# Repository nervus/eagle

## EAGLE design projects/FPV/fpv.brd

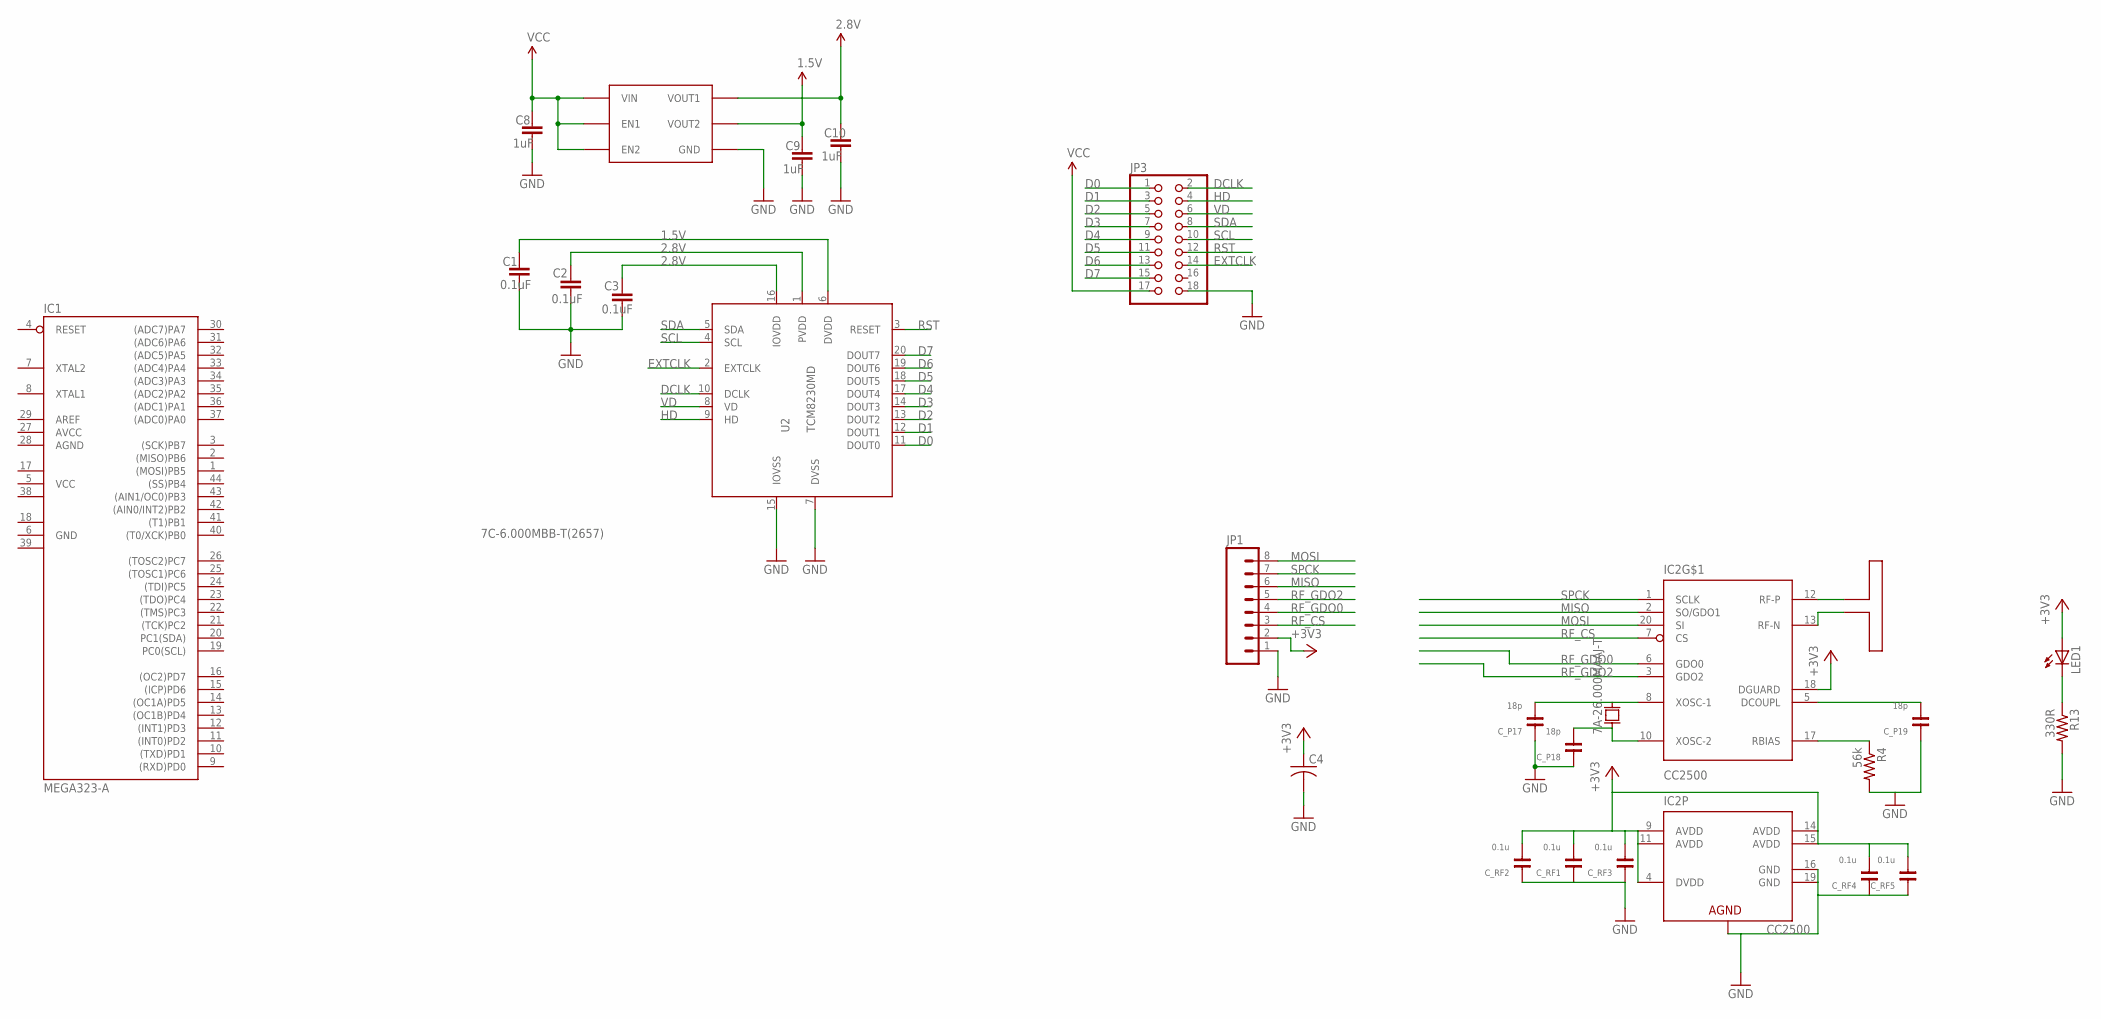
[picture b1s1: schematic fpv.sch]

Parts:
C1, C2, C3: 0.1uF; 0402-CAP
C4: C-USC1206; C1206
C8, C9, C10: 1uF; 0402-CAP
C_P17, C_P18, C_P19: 18p; 0603-CAP
C_RF1, C_RF2, C_RF3, C_RF4, C_RF5: 0.1u; 0603-CAP
IC1: MEGA323-A; TQFP44
IC2: CC2500; QLP-20
JP1: M081X08; 1X08
JP3: PINHD-2X9; 2X09
LED1: LED1206; LED-1206
R4: 56k; 0402-RES
R13: 330R; 0402-RES
U1: MIC5320; SOT23-6
U2: TCM8230MD
U$22: ANTENNA_DIPOLE; CC2500_FOLDED_DIPOLE_ANTENNA
U$23: 7A-26.000MAAJ-T; 5X3.2MM_SMD_XTAL

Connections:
1.5V: C1.1, C9.1, U1.5 (VOUT2), U2.6 (DVDD)
2.8V: C2.1, C3.1, C10.1, U1.4 (VOUT1), U2.1 (PVDD), U2.16 (IOVDD)
+3V3: C4.1, C_RF1.2, C_RF2.2, C_RF3.2, C_RF4.2, C_RF5.2, IC2.4 (DVDD), IC2.9 (AVDD), IC2.11 (AVDD), IC2.14 (AVDD), IC2.15 (AVDD), IC2.18 (DGUARD), JP1.2, LED1.A
AGND: IC1.28 (AGND)
AVCC: IC1.27 (AVCC)
D0: JP3.1, U2.11 (DOUT0)
D1: JP3.3, U2.12 (DOUT1)
D2: JP3.5, U2.13 (DOUT2)
D3: JP3.7, U2.14 (DOUT3)
D4: JP3.9, U2.17 (DOUT4)
D5: JP3.11, U2.18 (DOUT5)
D6: JP3.13, U2.19 (DOUT6)
D7: JP3.15, U2.20 (DOUT7)
DCLK: JP3.2, U2.10 (DCLK)
DCOUPL: C_P19.2, IC2.5 (DCOUPL)
EXTCLK: JP3.14, U2.2 (EXTCLK)
GND: C1.2, C2.2, C3.2, C4.2, C8.2, C9.2, C10.2, C_P17.1, C_P18.1, C_P19.1, C_RF1.1, C_RF2.1, C_RF3.1, C_RF4.1, C_RF5.1, IC1.6 (GND), IC2.16 (GND), IC2.19 (GND), IC2.PAD (AGND), IC2.THERMAL1 (AGND), IC2.THERMAL2 (AGND), IC2.THERMAL3 (AGND), IC2.THERMAL4 (AGND), IC2.THERMAL5 (AGND), JP1.1, JP3.18, R4.2, R13.2, U1.2 (GND), U2.7 (DVSS), U2.15 (IOVSS)
GND1: IC1.18 (GND1)
GND2: IC1.39 (GND2)
HD: JP3.4, U2.9 (HD)
MISO: IC2.2 (SO/GDO1), JP1.6
MOSI: IC2.20 (SI), JP1.8
unnamed: LED1.C, R13.1
unnamed: IC2.12 (RF-P), U$22.P$1
unnamed: IC2.13 (RF-N), U$22.P$2
unnamed: C_P17.2, IC2.8 (XOSC-1), U$23.X2
unnamed: C_P18.2, IC2.10 (XOSC-2), U$23.X1
unnamed: IC2.17 (RBIAS), R4.1
RF_CS: IC2.7 (CS), JP1.3
RF_GDO0: IC2.6 (GDO0), JP1.4
RF_GDO2: IC2.3 (GDO2), JP1.5
RST: JP3.12, U2.3 (RESET)
SCL: JP3.10, U2.4 (SCL)
SDA: JP3.8, U2.5 (SDA)
SPCK: IC2.1 (SCLK), JP1.7
VCC: C8.1, IC1.5 (VCC), JP3.17, U1.1 (EN2), U1.3 (VIN), U1.6 (EN1)
VCC1: IC1.17 (VCC1)
VCC2: IC1.38 (VCC2)
VD: JP3.6, U2.8 (VD)

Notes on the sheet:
7C-6.000MBB-T(2657)

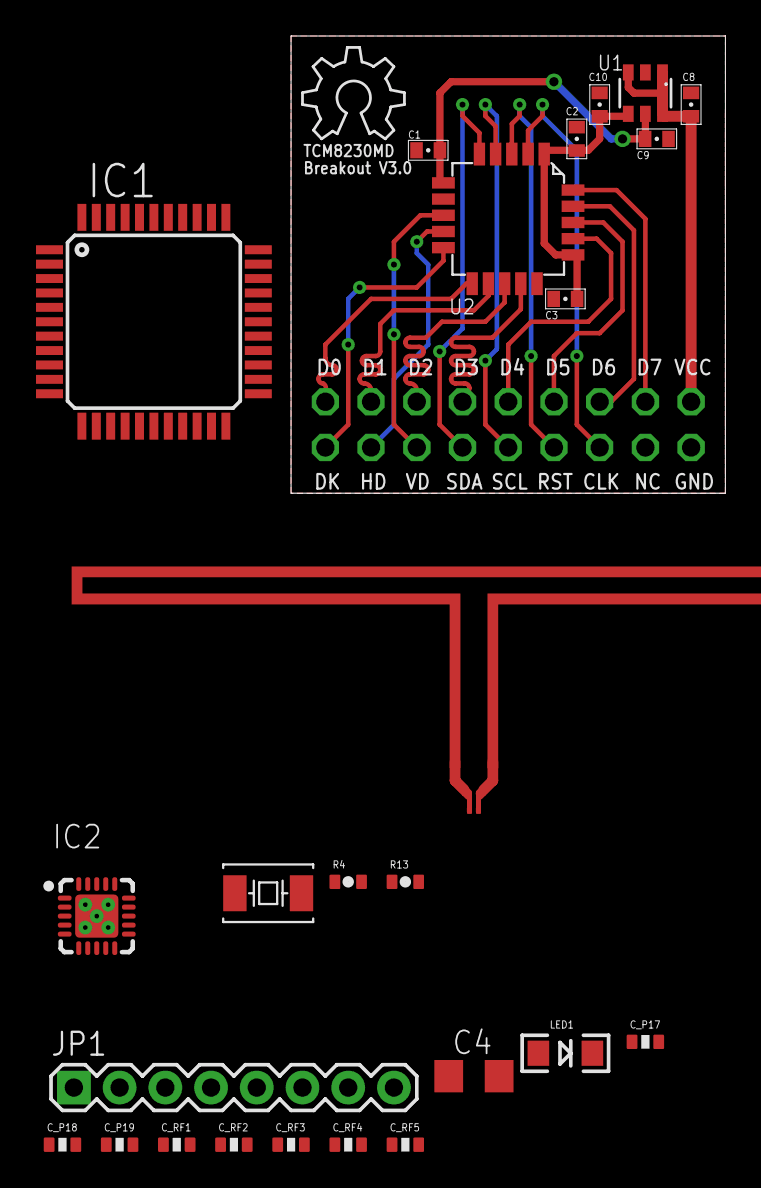
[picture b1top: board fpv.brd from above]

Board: 2 copper layers, 24.1 x 25.4 mm, 27 parts (1 on the bottom side), 33 nets.

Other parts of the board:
U$5: OSHW_6X200_NOTEXT

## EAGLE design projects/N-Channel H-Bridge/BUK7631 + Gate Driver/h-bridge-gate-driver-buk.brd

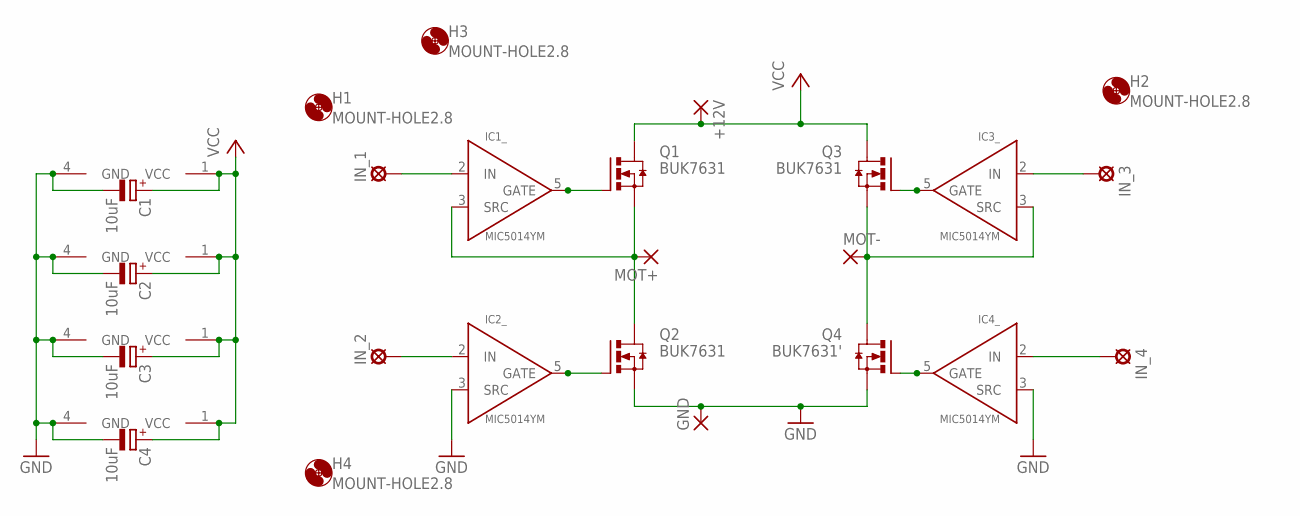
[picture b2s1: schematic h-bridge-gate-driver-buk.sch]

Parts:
+12V: WIREPAD4,16O1,6; 4,16O1,6
C1, C2, C3, C4: 10uF; UD-4X5,8_NICHICON
GND: WIREPAD4,16O1,6; 4,16O1,6
H1, H2, H3, H4: MOUNT-HOLE2.8; 2,8
IC1, IC2, IC3, IC4: MIC5014YM; SO8
IN_1, IN_2, IN_3, IN_4: LSP11
MOT+: WIREPAD4,16O1,6; 4,16O1,6
MOT-: WIREPAD4,16O1,6; 4,16O1,6
Q1, Q2, Q3: BUK7631; D2PAK_TO263
Q4: BUK7631'; D2PAK_TO263

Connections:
GND: C1.-, C2.-, C3.-, C4.-, GND.1, IC1.4 (GND), IC2.3 (SRC), IC2.4 (GND), IC3.4 (GND), IC4.3 (SRC), IC4.4 (GND), Q2.3 (S), Q4.3 (S)
MOT+: IC1.3 (SRC), MOT+.1, Q1.3 (S), Q2.4 (D)
MOT-: IC3.3 (SRC), MOT-.1, Q3.3 (S), Q4.4 (D)
unnamed: IC4.2 (IN), IN_4.MP
unnamed: IC3.5 (GATE), Q3.1 (G)
unnamed: IC1.2 (IN), IN_1.MP
unnamed: IC3.2 (IN), IN_3.MP
unnamed: IC2.2 (IN), IN_2.MP
unnamed: IC1.5 (GATE), Q1.1 (G)
unnamed: IC4.5 (GATE), Q4.1 (G)
unnamed: IC2.5 (GATE), Q2.1 (G)
VCC: +12V.1, C1.+, C2.+, C3.+, C4.+, IC1.1 (VCC), IC2.1 (VCC), IC3.1 (VCC), IC4.1 (VCC), Q1.4 (D), Q3.4 (D)

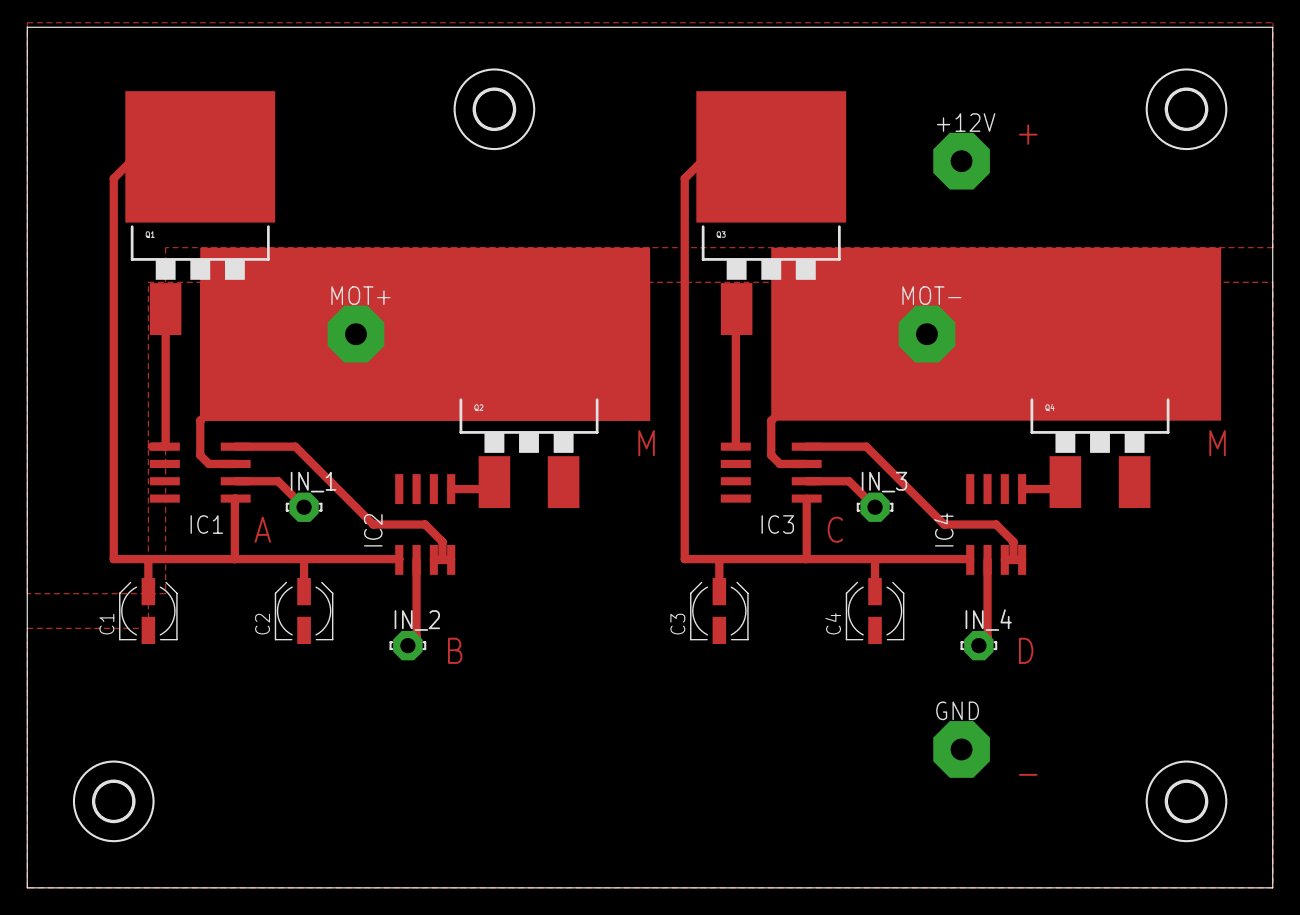
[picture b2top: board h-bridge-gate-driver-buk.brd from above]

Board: 2 copper layers, 91.4 x 63.2 mm, 24 parts (0 on the bottom side), 12 nets.

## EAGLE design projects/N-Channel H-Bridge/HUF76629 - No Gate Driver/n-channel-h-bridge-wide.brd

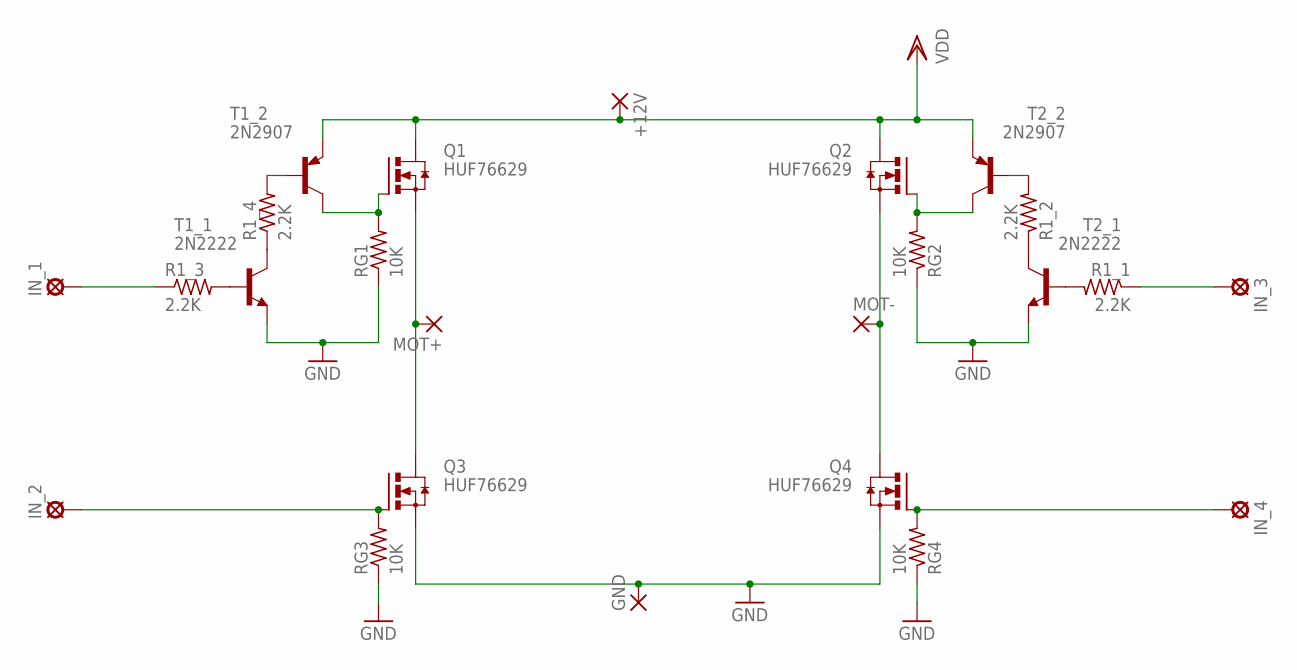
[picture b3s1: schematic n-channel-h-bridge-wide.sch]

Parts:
+12V: WIREPAD4,16O1,6; 4,16O1,6
GND: WIREPAD4,16O1,6; 4,16O1,6
IN_1, IN_2, IN_3, IN_4: LSP11
MOT+: WIREPAD4,16O1,6; 4,16O1,6
MOT-: WIREPAD4,16O1,6; 4,16O1,6
Q1, Q2, Q3, Q4: HUF76629; D-PAK_TO252
R1_1, R1_2, R1_3, R1_4: 2.2K; R0805
RG1, RG2, RG3, RG4: 10K; R0805
T1_1, T2_1: 2N2222; TO92-EBC-OVAL
T1_2, T2_2: 2N2907; TO92-EBC-OVAL

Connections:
B: IN_2.MP, Q3.1 (G), RG3.2
D: IN_4.MP, Q4.1 (G), RG4.2
GND: GND.1, Q3.3 (S), Q4.3 (S), RG1.1, RG2.1, RG3.1, RG4.1, T1_1.E, T2_1.E
unnamed: R1_1.2, T2_1.B
unnamed: R1_2.1, T2_1.C
unnamed: R1_2.2, T2_2.B
unnamed: Q2.1 (G), RG2.2, T2_2.C
unnamed: MOT-.1, Q2.3 (S), Q4.4 (D)
unnamed: IN_1.MP, R1_3.1
unnamed: IN_3.MP, R1_1.1
unnamed: R1_3.2, T1_1.B
unnamed: R1_4.1, T1_1.C
unnamed: R1_4.2, T1_2.B
unnamed: Q1.1 (G), RG1.2, T1_2.C
unnamed: MOT+.1, Q1.3 (S), Q3.4 (D)
VDD: +12V.1, Q1.4 (D), Q2.4 (D), T1_2.E, T2_2.E

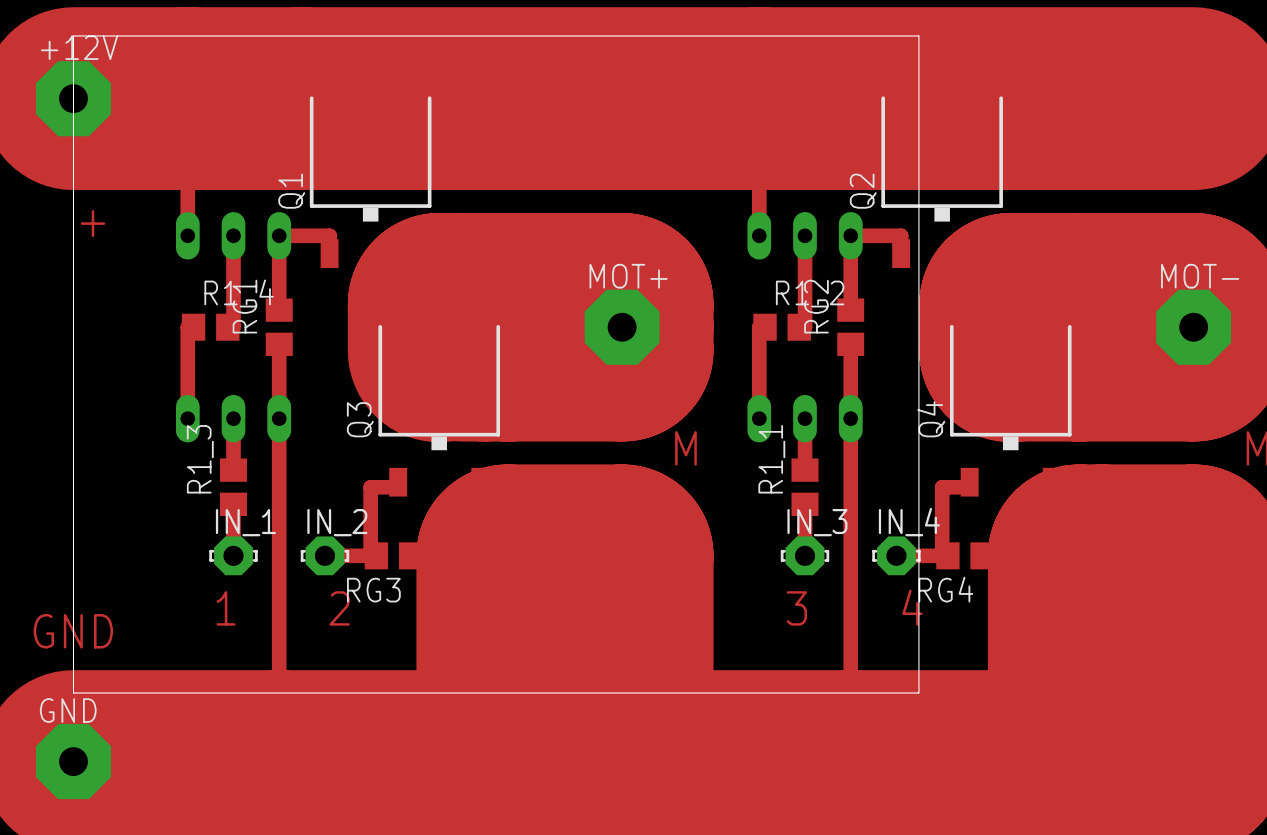
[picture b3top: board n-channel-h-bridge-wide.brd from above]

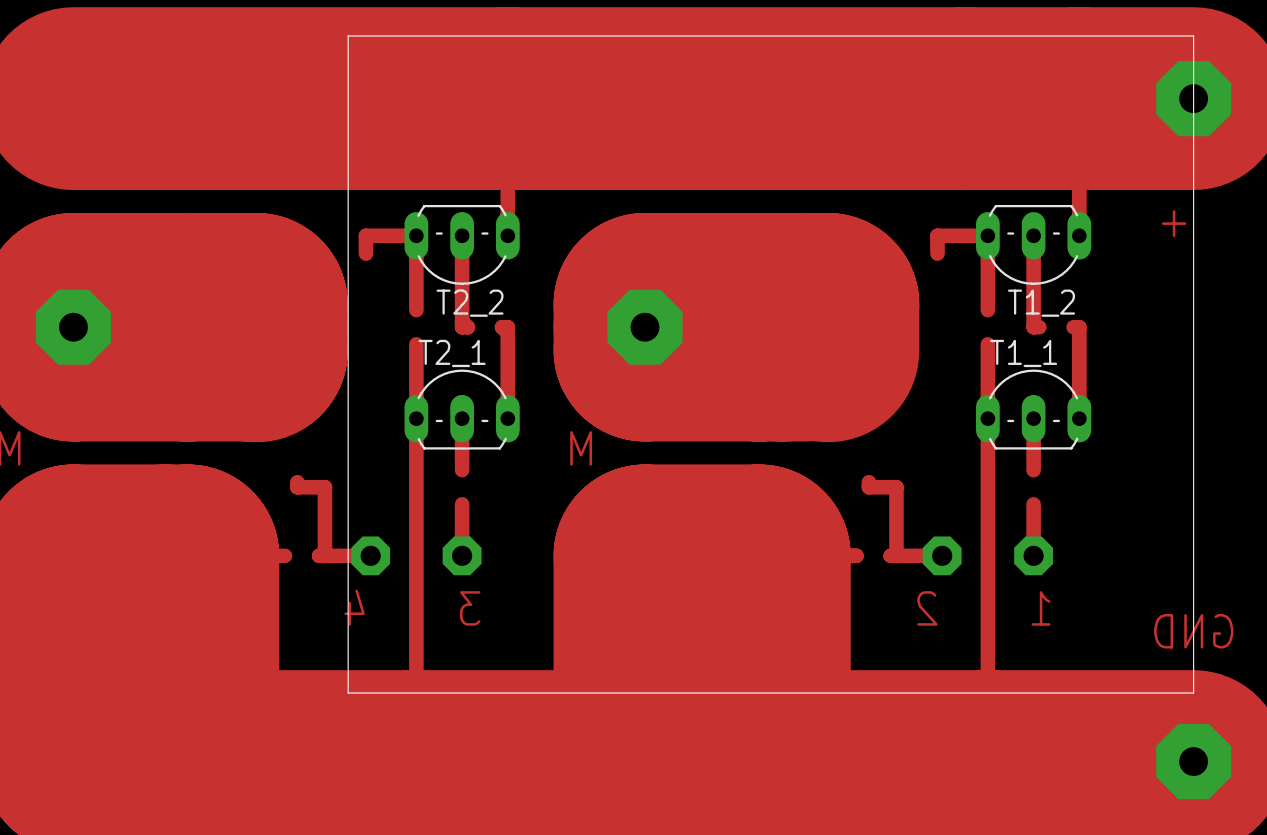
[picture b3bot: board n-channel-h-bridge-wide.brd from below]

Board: 2 copper layers, 24 parts (4 on the bottom side), 16 nets.

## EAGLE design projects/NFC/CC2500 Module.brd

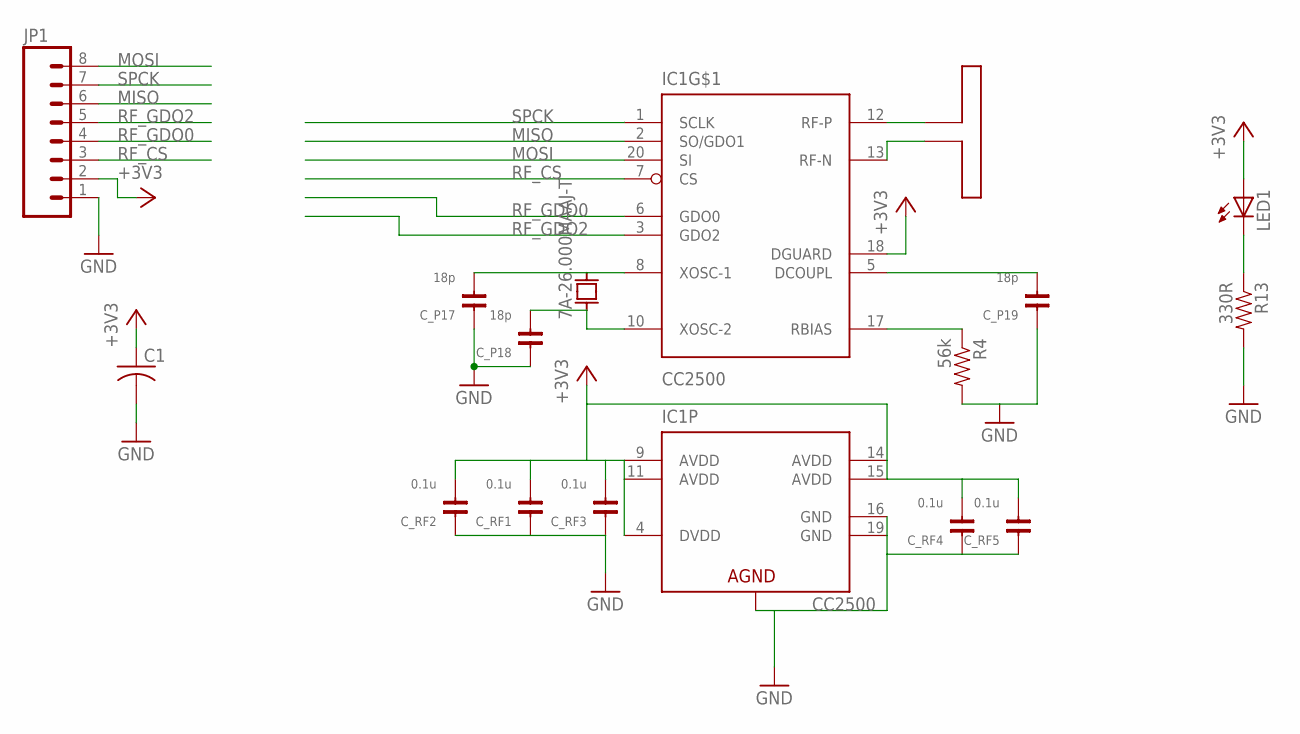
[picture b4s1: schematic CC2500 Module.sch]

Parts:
C1: C-USC1206; C1206
C_P17, C_P18, C_P19: 18p; 0603-CAP
C_RF1, C_RF2, C_RF3, C_RF4, C_RF5: 0.1u; 0603-CAP
IC1: CC2500; QLP-20
JP1: M081X08; 1X08
LED1: LED1206; LED-1206
R4: 56k; 0402-RES
R13: 330R; 0402-RES
U$22: ANTENNA_DIPOLE; CC2500_FOLDED_DIPOLE_ANTENNA
U$23: 7A-26.000MAAJ-T; 5X3.2MM_SMD_XTAL

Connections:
+3V3: C1.1, C_RF1.2, C_RF2.2, C_RF3.2, C_RF4.2, C_RF5.2, IC1.4 (DVDD), IC1.9 (AVDD), IC1.11 (AVDD), IC1.14 (AVDD), IC1.15 (AVDD), IC1.18 (DGUARD), JP1.2, LED1.A
DCOUPL: C_P19.2, IC1.5 (DCOUPL)
GND: C1.2, C_P17.1, C_P18.1, C_P19.1, C_RF1.1, C_RF2.1, C_RF3.1, C_RF4.1, C_RF5.1, IC1.16 (GND), IC1.19 (GND), IC1.PAD (AGND), IC1.THERMAL1 (AGND), IC1.THERMAL2 (AGND), IC1.THERMAL3 (AGND), IC1.THERMAL4 (AGND), IC1.THERMAL5 (AGND), JP1.1, R4.2, R13.2
MISO: IC1.2 (SO/GDO1), JP1.6
MOSI: IC1.20 (SI), JP1.8
unnamed: LED1.C, R13.1
unnamed: IC1.12 (RF-P), U$22.P$1
unnamed: IC1.13 (RF-N), U$22.P$2
unnamed: C_P17.2, IC1.8 (XOSC-1), U$23.X2
unnamed: C_P18.2, IC1.10 (XOSC-2), U$23.X1
unnamed: IC1.17 (RBIAS), R4.1
RF_CS: IC1.7 (CS), JP1.3
RF_GDO0: IC1.6 (GDO0), JP1.4
RF_GDO2: IC1.3 (GDO2), JP1.5
SPCK: IC1.1 (SCLK), JP1.7

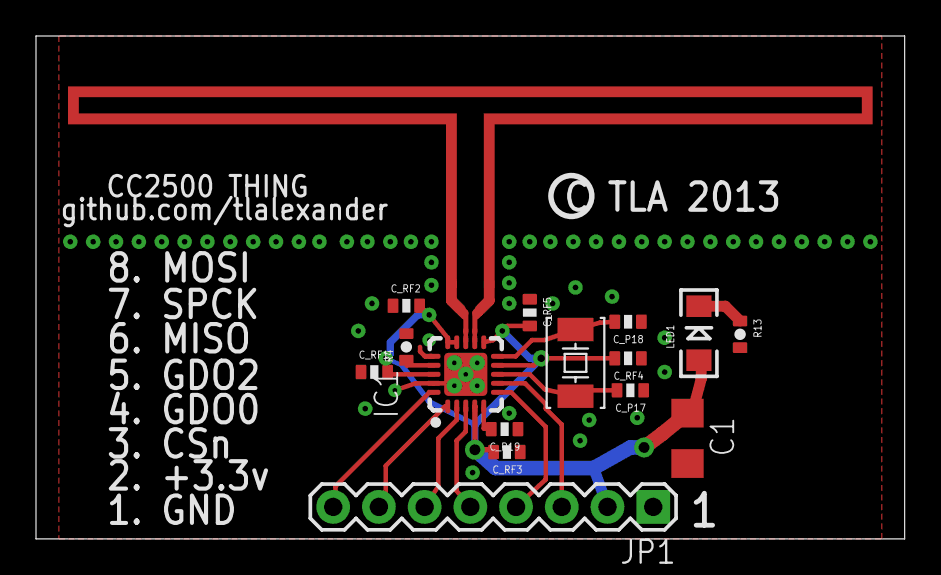
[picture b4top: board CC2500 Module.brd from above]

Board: 2 copper layers, 48.3 x 27.9 mm, 16 parts (0 on the bottom side), 15 nets.

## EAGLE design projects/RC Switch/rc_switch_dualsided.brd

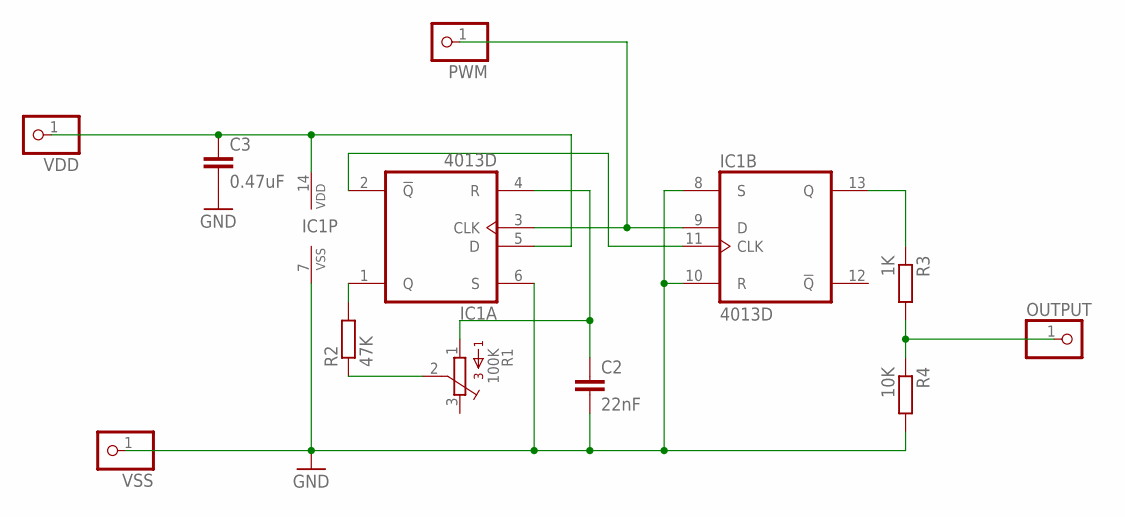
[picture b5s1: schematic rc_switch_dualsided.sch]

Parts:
C2: 22nF; C3216
C3: 0.47uF; C3216
IC1: 4013D; SO14
OUTPUT: PINHD-1X1; 1X01
PWM: PINHD-1X1; 1X01
R1: 100K; 3386P
R2: 47K; R3225
R3: 1K; R3225
R4: 10K; R3225
VDD: PINHD-1X1; 1X01
VSS: PINHD-1X1; 1X01

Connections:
GND: C2.2, C3.2, IC1.6 (S), IC1.7 (VSS), IC1.8 (S), IC1.10 (R), R4.2, VSS.1
unnamed: IC1.1 (Q), R2.2
unnamed: R1.2, R2.1
unnamed: C2.1, IC1.4 (R), R1.1
unnamed: IC1.13 (Q), R3.1
unnamed: IC1.3 (CLK), IC1.9 (D), PWM.1
unnamed: IC1.2 (!Q), IC1.11 (CLK)
unnamed: C3.1, IC1.5 (D), IC1.14 (VDD), VDD.1
OUTPUT: OUTPUT.1, R3.2, R4.1

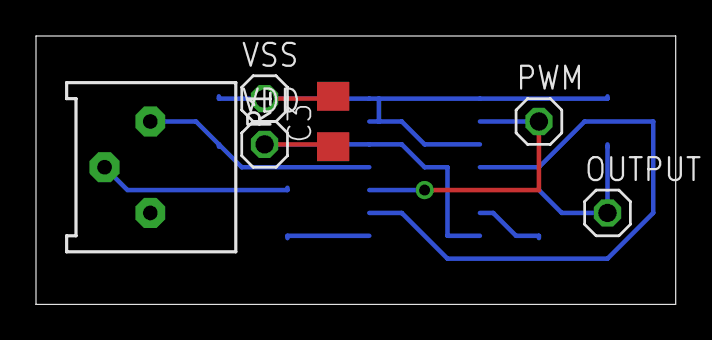
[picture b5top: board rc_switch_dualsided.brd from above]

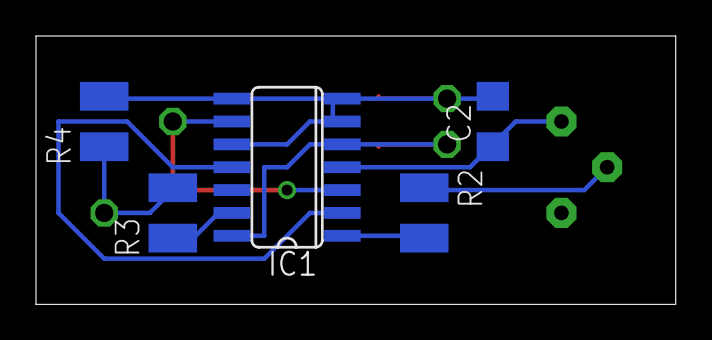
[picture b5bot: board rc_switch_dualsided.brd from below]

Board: 2 copper layers, 35.5 x 14.9 mm, 11 parts (5 on the bottom side), 9 nets.

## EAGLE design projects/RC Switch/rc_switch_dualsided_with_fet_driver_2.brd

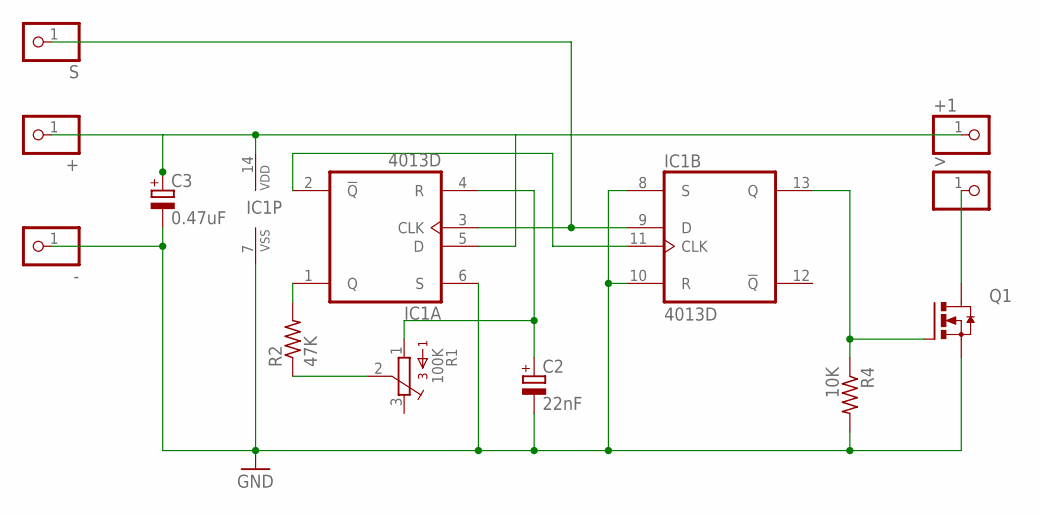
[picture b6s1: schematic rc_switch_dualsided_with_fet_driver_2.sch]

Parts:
+, +1: PINHD-1X1; 1X01
-: PINHD-1X1; 1X01
>: PINHD-1X1; 1X01
C2: 22nF; PANASONIC_A
C3: 0.47uF; PANASONIC_A
IC1: 4013D; SO14
Q1: HUF76629D3ST_F085D-PAK_TO252; D-PAK_TO252
R1: 100K; 3386P
R2: 47K; R0805W
R4: 10K; R0805W
S: PINHD-1X1; 1X01

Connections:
GND: -.1, C2.-, C3.-, IC1.6 (S), IC1.7 (VSS), IC1.8 (S), IC1.10 (R), Q1.3 (S), R4.2
unnamed: IC1.1 (Q), R2.2
unnamed: R1.2, R2.1
unnamed: C2.+, IC1.4 (R), R1.1
unnamed: IC1.2 (!Q), IC1.11 (CLK)
OUT-: >.1, Q1.4 (D)
OUTPUT: IC1.13 (Q), Q1.1 (G), R4.1
SIG_IN: IC1.3 (CLK), IC1.9 (D), S.1
VDD: +.1, +1.1, C3.+, IC1.5 (D), IC1.14 (VDD)

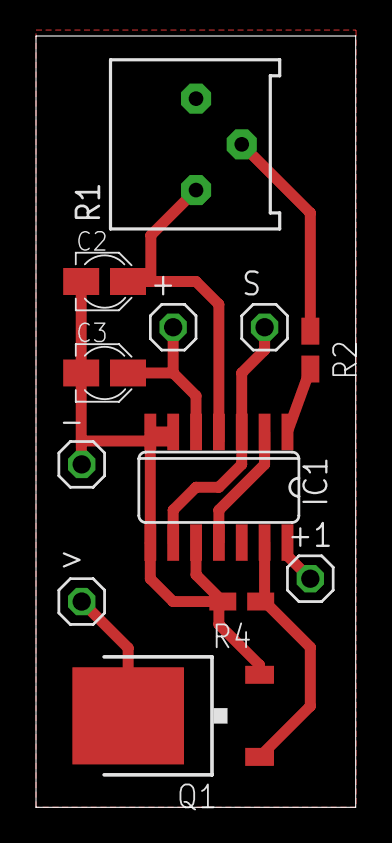
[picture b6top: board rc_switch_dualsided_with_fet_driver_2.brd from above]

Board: 2 copper layers, 17.8 x 42.9 mm, 12 parts (0 on the bottom side), 9 nets.
